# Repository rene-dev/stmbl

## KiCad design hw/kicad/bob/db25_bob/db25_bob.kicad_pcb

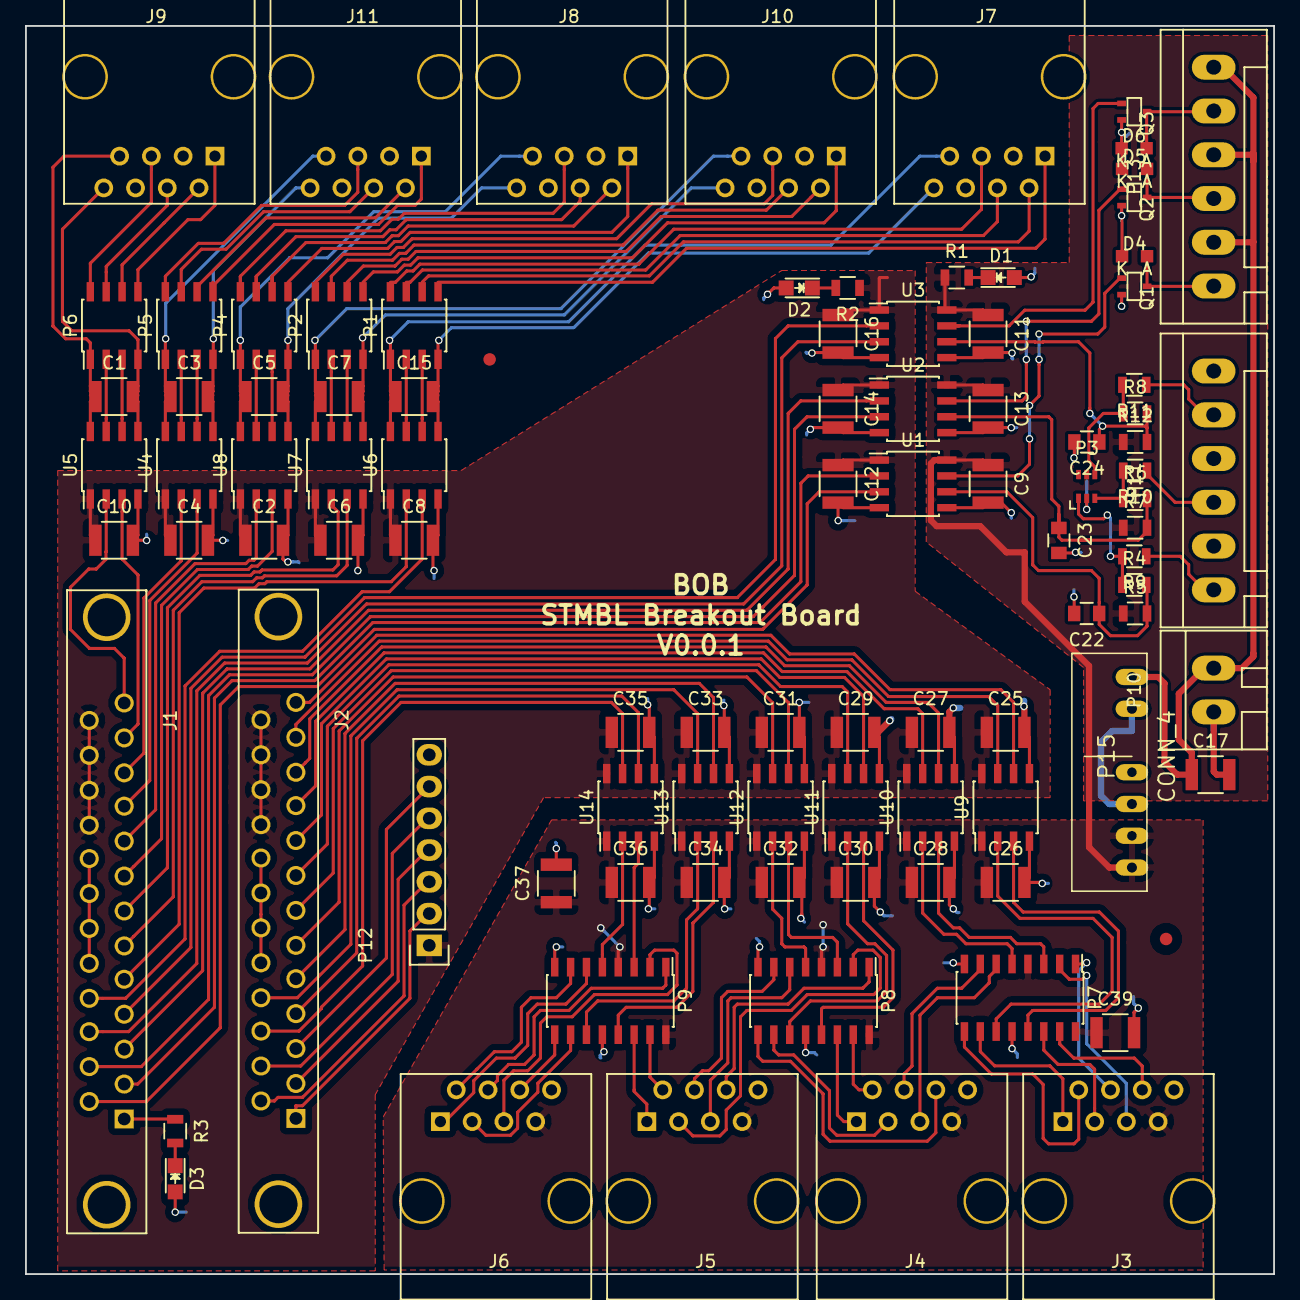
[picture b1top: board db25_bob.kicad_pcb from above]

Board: 2 copper layers, 99.8 x 99.8 mm, 94 parts (0 on the bottom side), 133 nets.

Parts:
C1, C2, C3, C4, C5, C6, C7, C8, C9, C10, C11, C12, C13, C14, C15, C16, C17, C25, C26, C27, C28, C29, C30, C31, C32, C33, C34, C35, C36, C37, C39: C; C_1210
C22, C23, C24: C; C_0805
D1, D2, D3: LED; LED-0805
D4, D5, D6: DIODE; MiniMELF_Standard
J1, J2: DB25; DB25FD
J3, J4, J5, J6, J7, J8, J9, J10, J11: RJ45; RJ45_8
P1, P2, P4, P5, P6: DIL8; SOIC-8_3.9x4.9mm_Pitch1.27mm
P3: DIL6; SC-70-6
P7, P8, P9: DIL16; SOIC-16_3.9x9.9mm_Pitch1.27mm
P10: CONN_2; WAGO_734_2pin_Straight_RuggedPads
P11, P13: CONN_6; WAGO_734_6pin_Straight_RuggedPads
P12: CONN_7; Socket_Strip_Straight_1x07
P15: CONN_4; SIP7
Q1, Q2, Q3: FET_N; sc70
R1, R2, R3, R4, R5, R6, R7, R8, R9, R10, R11, R12: R; R_0805
U1, U2, U3, U4, U5, U6, U7, U8: ADuM1201WT; SOIC-8_3.9x4.9mm_Pitch1.27mm
U9, U10, U11, U12, U13, U14: ADuM1200CR; SOIC-8_3.9x4.9mm_Pitch1.27mm

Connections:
0RX: P1.2, U6.7
0RX+: J7.5, P1.8
0RX-: J7.4, P1.7
0TX: P1.3, U6.6
0TX+: J7.1, P1.5
0TX-: J7.2, P1.6
1RX: P2.2, U7.7
1RX+: J10.5, P2.8
1RX-: J10.4, P2.7
1TX: P2.3, U7.6
1TX+: J10.1, P2.5
1TX-: J10.2, P2.6
2RX: P4.2, U8.7
2RX+: J8.5, P4.8
2RX-: J8.4, P4.7
2TX: P4.3, U8.6
2TX+: J8.1, P4.5
2TX-: J8.2, P4.6
3RX: P5.2, U4.7
3RX+: J11.5, P5.8
3RX-: J11.4, P5.7
3TX: P5.3, U4.6
3TX+: J11.1, P5.5
3TX-: J11.2, P5.6
4RX: P6.2, U5.7
4RX+: J9.5, P6.8
4RX-: J9.4, P6.7
4TX: P6.3, U5.6
4TX+: J9.1, P6.5
4TX-: J9.2, P6.6
5V0: C15.1, J7.7, P1.1, U6.8
5V1: C7.1, J10.7, P2.1, U7.8
5V2: C5.1, J8.7, P4.1, U8.8
5V3: C3.1, J11.7, P5.1, U4.8
5V4: C1.1, J9.7, P6.1, U5.8
+5V: C2.1, C4.1, C6.1, C8.1, C10.1, C12.1, C14.1, C16.1, C25.1, C27.1, C29.1, C31.1, C33.1, C35.1, J1.22, J1.23, J1.24, J1.25, J2.22, J2.23, J2.24, J2.25, P12.1, R2.1, U1.1, U2.1, U3.1, U4.1, U5.1, U6.1, U7.1, U8.1, U9.8, U10.8, U11.8, U12.8, U13.8, U14.8
+5VA: C9.1, C11.1, C13.1, C26.1, C28.1, C30.1, C32.1, C34.1, C36.1, C37.1, C39.1, J3.7, J4.7, J5.7, J6.7, P3.5, P7.4, P7.16, P8.4, P8.16, P9.4, P9.16, P15.4, R1.1, R5.1, R7.1, R12.1, U1.8, U2.8, U3.8, U9.1, U10.1, U11.1, U12.1, U13.1, U14.1
+24V: C17.1, P10.2, P13.2, P13.4, P13.6, P15.1
EN-: C9.2, C11.2, C13.2, C17.2, C22.2, C23.2, C24.2, C26.2, C28.2, C30.2, C32.2, C34.2, C36.2, C37.2, C39.2, D1.2, D4.1, D5.1, D6.1, J3.8, J4.8, J5.8, J6.8, P3.2, P7.8, P7.12, P8.8, P8.12, P9.8, P9.12, P10.1, P11.2, P11.4, P11.6, P15.2, P15.3, Q1.S, Q2.S, Q3.S, U1.5, U2.5, U3.5, U9.4, U10.4, U11.4, U12.4, U13.4, U14.4
ENC0A: P7.11, U9.2
ENC0A+: J3.1, P7.10
ENC0A-: J3.2, P7.9
ENC0AO: J2.12, U9.7
ENC0B: P7.13, U9.3
ENC0B+: J3.3, P7.14
ENC0B-: J3.6, P7.15
ENC0BO: J2.13, U9.6
ENC0Z: P7.3, U10.3
ENC0Z+: J3.5, P7.2
ENC0Z-: J3.4, P7.1
ENC0ZO: J2.11, U10.6
ENC1A: P8.13, U11.3
ENC1A+: J4.1, P8.14
ENC1A-: J4.2, P8.15
ENC1AO: J2.9, U11.6
ENC1B: P8.11, U11.2
ENC1B+: J4.3, P8.10
ENC1B-: J4.6, P8.9
ENC1BO: J2.8, U11.7
ENC1Z: P7.5, U10.2
ENC1Z+: J4.5, P7.6
ENC1Z-: J4.4, P7.7
ENC1ZO: J2.10, U10.7
ENC2A: P9.13, U13.3
ENC2A+: J5.1, P9.14
ENC2A-: J5.2, P9.15
ENC2AO: J2.5, U13.6
ENC2B: P8.3, U12.3
ENC2B+: J5.3, P8.2
ENC2B-: J5.6, P8.1
ENC2BO: J2.7, U12.6
ENC2Z: P8.5, U12.2
ENC2Z+: J5.5, P8.6
ENC2Z-: J5.4, P8.7
ENC2ZO: J2.6, U12.7
ENC3A: P9.5, U14.2
ENC3A+: J6.1, P9.6
ENC3A-: J6.2, P9.7
ENC3AO: J2.16, U14.7
ENC3B: P9.11, U13.2
ENC3B+: J6.3, P9.10
ENC3B-: J6.6, P9.9
ENC3BO: J2.17, U13.7
ENC3Z: P9.3, U14.3
ENC3Z+: J6.5, P9.2
ENC3Z-: J6.4, P9.1
ENC3ZO: J2.4, U14.6
GND: C2.2, C4.2, C6.2, C8.2, C10.2, C12.2, C14.2, C16.2, C25.2, C27.2, C29.2, C31.2, C33.2, C35.2, D2.2, D3.2, J1.18, J1.19, J1.20, J1.21, J2.18, J2.19, J2.20, J2.21, P12.7, U1.4, U2.4, U3.4, U4.4, U5.4, U6.4, U7.4, U8.4, U9.5, U10.5, U11.5, U12.5, U13.5, U14.5
GND0: C15.2, J7.8, P1.4, U6.5
GND1: C7.2, J10.8, P2.4, U7.5
GND2: C5.2, J8.8, P4.4, U8.5
GND3: C3.2, J11.8, P5.4, U4.5
GND4: C1.2, J9.8, P6.4, U5.5
IN0: P11.1, R9.1
IN0P: C22.1, R4.2, R5.2, U1.6
IN0R: P3.1, R4.1, R9.2
IN1: P11.3, R10.1
IN1P: C23.1, R6.2, R7.2, U2.6
IN1R: P3.3, R6.1, R10.2
IN2: P11.5, R11.1
IN2P: C24.1, R8.2, R12.2, U3.6
IN2R: P3.4, R8.1, R11.2
IO0: J1.17, U6.3
IO1: J1.5, U6.2
IO2: J1.6, U7.3
IO3: J1.7, U7.2
IO4: J1.8, U8.3
IO5: J1.9, U8.2
IO6: J1.10, U4.3
IO7: J1.11, U4.2
IO8: J1.12, U5.3
IO9: J1.13, U5.2
IO10: J1.14, U1.3
IO11: J1.2, U1.2
IO12: J1.15, U2.3
IO13: J1.3, U2.2
IO14: J1.16, U3.3
IO15: J1.4, U3.2
IO16: J1.1, R3.1
unnamed: D1.1, R1.2
unnamed: D2.1, R2.2
unnamed: D3.1, R3.2
unnamed: J2.1, P12.2
unnamed: J2.2, P12.4
unnamed: J2.3, P12.6
unnamed: J2.14, P12.3
unnamed: J2.15, P12.5
OUT0: Q1.G, U1.7
OUT0FET: D4.2, P13.1, Q1.D
OUT1: Q2.G, U2.7
OUT1FET: D5.2, P13.3, Q2.D
OUT2: Q3.G, U3.7
OUT2FET: D6.2, P13.5, Q3.D

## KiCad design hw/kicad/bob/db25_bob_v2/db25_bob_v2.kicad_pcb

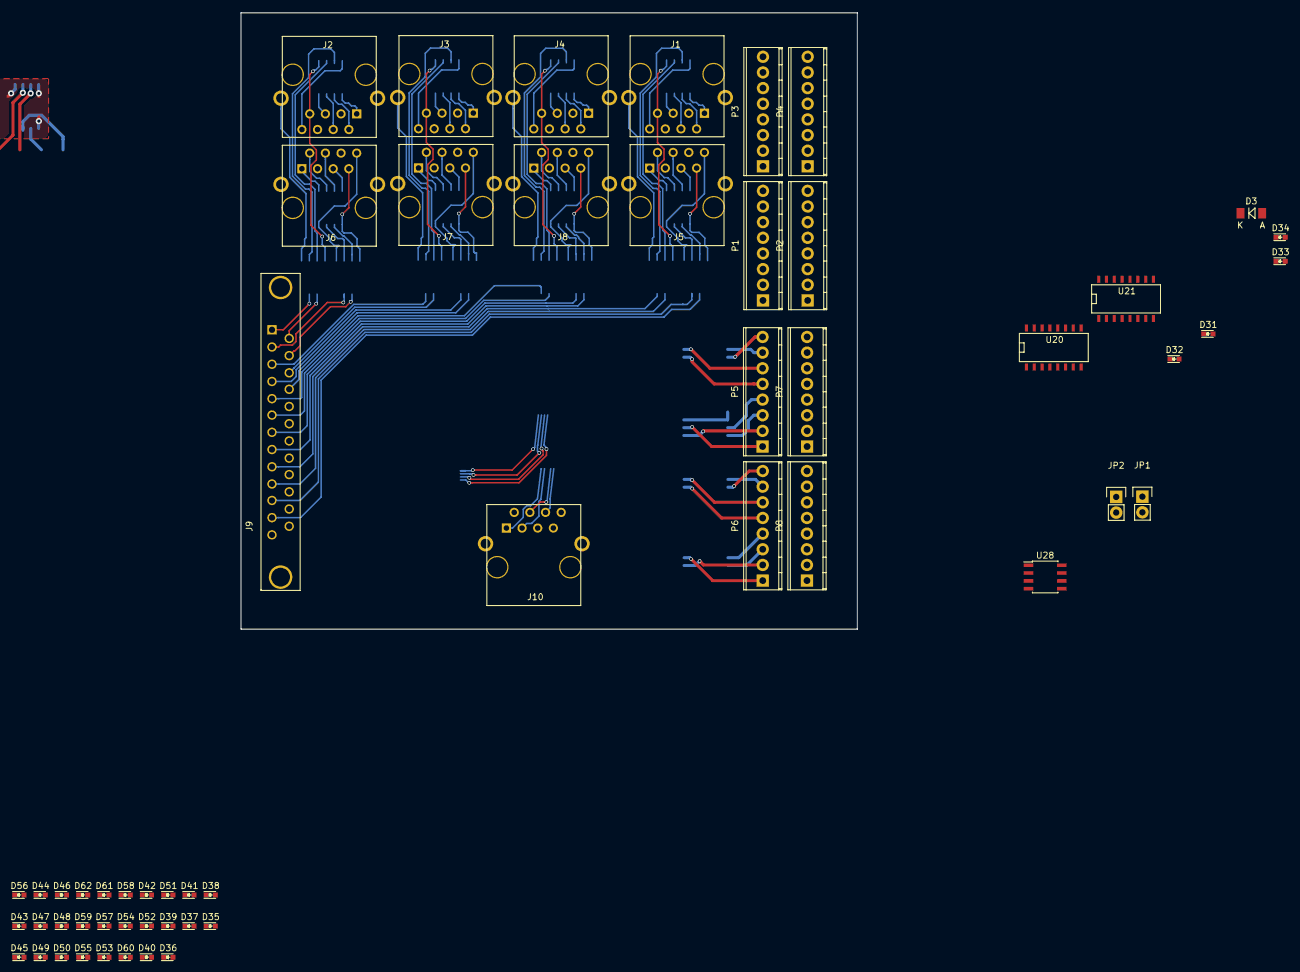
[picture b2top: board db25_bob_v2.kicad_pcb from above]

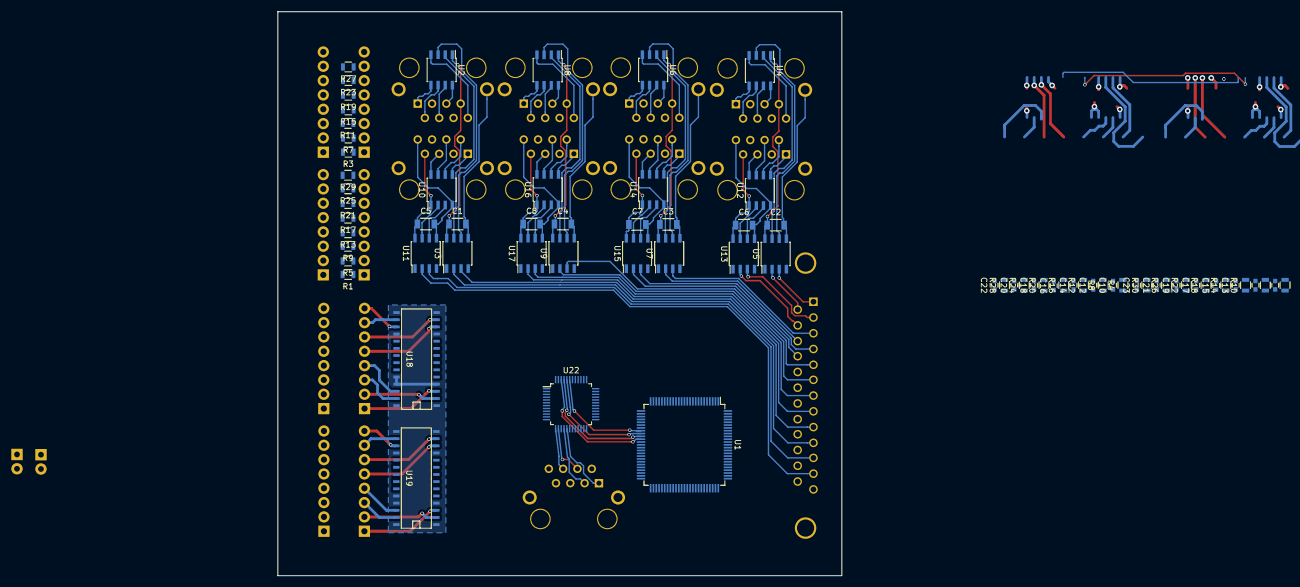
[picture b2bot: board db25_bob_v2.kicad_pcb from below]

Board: 2 copper layers, 100.0 x 100.0 mm, 129 parts (73 on the bottom side), 157 nets.

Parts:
C1, C2, C3, C4, C5, C6, C7, C8: C; C_1206
C9, C10, C11, C12, C13, C14, C15, C16, C17, C18, C19, C20, C21, C22, C23: C; C_0603
D3: D; MiniMELF_Standard
D31, D32, D33, D34, D35, D36, D37, D38, D39, D40, D41, D42, D43, D44, D45, D46, D47, D48, D49, D50, D51, D52, D53, D54, D55, D56, D57, D58, D59, D60, D61, D62: LED; LED_0603
J1, J2, J3, J4, J5, J6, J7, J8: RJ45; MHRJJ88NFVS
J9: DB25; DB25FD
J10: RJ45-TRANSFO; MHRJJ88NFVS
JP1, JP2: JUMPER; Pin_Header_Straight_1x02
P1, P2, P3, P4, P5, P6, P7, P8: CONN_01X08; TerminalBlock_Pheonix_MPT-2.54mm_8pol
R1, R2, R3, R4, R5, R6, R7, R8, R9, R10, R11, R12, R13, R14, R15, R16, R17, R18, R19, R20, R21, R22, R23, R24, R25, R26, R27, R28, R29, R30: R; R_0805
U1: STM32F407VG; TQFP-100_14x14mm_Pitch0.5mm
U2, U4, U6, U8, U10, U12, U14, U16: ADM4857; SOIC-8_3.9x4.9mm_Pitch1.27mm
U3, U5, U7, U9, U11, U13, U15, U17, U28: ADuM1201WT; SOIC-8_3.9x4.9mm_Pitch1.27mm
U18, U19: NCV7608; SOIC-28
U20, U21: 74HC595; SO-16-N
U22: DP83848C; LQFP-48_7x7mm_Pitch0.5mm

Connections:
5V1: C2.1, J2.7, U4.1, U5.8
5V2: C6.1, J6.7, U12.1, U13.8
5V3: C3.1, J3.7, U6.1, U7.8
5V4: C7.1, J7.7, U14.1, U15.8
5V5: C4.1, J4.7, U8.1, U9.8
5V6: C8.1, J8.7, U16.1, U17.8
5V7: C1.1, J1.7, U2.1, U3.8
5V8: C5.1, J5.7, U10.1, U11.8
+3V3: D3.1, U18.8, U19.8
+5VD: J9.22, J9.23, J9.24, J9.25, U3.1, U5.1, U7.1, U9.1, U11.1, U13.1, U15.1, U17.1, U28.1
+24V: U18.1, U18.4, U18.11, U18.14, U18.15, U18.18, U18.24, U18.25, U18.28, U19.1, U19.4, U19.11, U19.14, U19.15, U19.18, U19.24, U19.25, U19.28
AIN1: P1.1, R1.2
AIN2: P1.2, R5.2
AIN3: P1.3, R9.2
AIN4: P1.4, R13.2
AIN5: P1.5, R17.2
AIN6: P1.6, R21.2
AIN7: P1.7, R25.2
AIN8: P1.8, R29.2
AIN9: P3.1, R3.2
AIN10: P3.2, R7.2
AIN11: P3.3, R11.2
AIN12: P3.4, R15.2
AIN13: P3.5, R19.2
AIN14: P3.6, R23.2
AIN15: P3.7, R27.2
CSB: U18.5, U19.5
EN: U18.19, U19.19
GND: C9.2, C10.2, C11.2, C12.2, C13.2, C14.2, C15.2, C16.2, C17.2, C18.2, C19.2, C20.2, C21.2, C22.2, C23.2, P2.1, P2.2, P2.3, P2.4, P2.5, P2.6, P2.7, P2.8, P4.1, P4.2, P4.3, P4.4, P4.5, P4.6, P4.7, P4.8, P7.1, P7.2, P7.3, P7.4, P7.5, P7.6, P7.7, P7.8, P8.1, P8.2, P8.3, P8.4, P8.5, P8.6, P8.7, P8.8, R2.2, R4.2, R6.2, R8.2, R10.2, R12.2, R14.2, R16.2, R18.2, R20.2, R22.2, R24.2, R26.2, R28.2, R30.2, U18.10, U19.10, U20.8, U21.8
GND1: C2.2, J2.8, U4.4, U5.5
GND2: C6.2, J6.8, U12.4, U13.5
GND3: C3.2, J3.8, U6.4, U7.5
GND4: C7.2, J7.8, U14.4, U15.5
GND5: C4.2, J4.8, U8.4, U9.5
GND6: C8.2, J8.8, U16.4, U17.5
GND7: C1.2, J1.8, U2.4, U3.5
GND8: C5.2, J5.8, U10.4, U11.5
GNDD: J9.18, J9.19, J9.20, J9.21, U3.4, U5.4, U7.4, U9.4, U11.4, U13.4, U15.4, U17.4, U28.4
IN0: J9.1, U5.3
IN1: J9.2, U13.3
IN1_ADC: C9.1, R1.1, R2.1
IN2: J9.3, U7.3
IN2_ADC: C11.1, R5.1, R6.1
IN3: J9.4, U15.3
IN3_ADC: C13.1, R9.1, R10.1
IN4: J9.5, U9.3
IN4_ADC: C15.1, R13.1, R14.1
IN5: J9.7, U17.3
IN5_ADC: C17.1, R17.1, R18.1
IN6: J9.9, U3.3
IN6_ADC: C19.1, R21.1, R22.1
IN7: J9.11, JP1.1, U11.3
IN7_ADC: C21.1, R25.1, R26.1
IN9_ADC: C10.1, D3.2, R3.1, R4.1
IN10_ADC: C12.1, R7.1, R8.1
IN11_ADC: C14.1, R11.1, R12.1
IN12_ADC: C16.1, R15.1, R16.1
IN13_ADC: C18.1, R19.1, R20.1
IN14_ADC: C20.1, R23.1, R24.1
IN15_ADC: C22.1, R27.1, R28.1
IN18ADC: C23.1, R29.1, R30.1
unnamed: J1.1, U2.5
unnamed: J1.2, U2.6
unnamed: J1.4, U2.7
unnamed: J1.5, U2.8
unnamed: J2.1, U4.5
unnamed: J2.2, U4.6
unnamed: J2.4, U4.7
unnamed: J2.5, U4.8
unnamed: J3.1, U6.5
unnamed: J3.2, U6.6
unnamed: J3.4, U6.7
unnamed: J3.5, U6.8
unnamed: J4.1, U8.5
unnamed: J4.2, U8.6
unnamed: J4.4, U8.7
unnamed: J4.5, U8.8
unnamed: J5.1, U10.5
unnamed: J5.2, U10.6
unnamed: J5.4, U10.7
unnamed: J5.5, U10.8
unnamed: J6.1, U12.5
unnamed: J6.2, U12.6
unnamed: J6.4, U12.7
unnamed: J6.5, U12.8
unnamed: J7.1, U14.5
unnamed: J7.2, U14.6
unnamed: J7.4, U14.7
unnamed: J7.5, U14.8
unnamed: J8.1, U16.5
unnamed: J8.2, U16.6
unnamed: J8.4, U16.7
unnamed: J8.5, U16.8
unnamed: JP1.2, U28.3
unnamed: JP2.2, U28.2
unnamed: U2.2, U3.7
unnamed: U2.3, U3.6
unnamed: U4.2, U5.7
unnamed: U4.3, U5.6
unnamed: U6.2, U7.7
unnamed: U6.3, U7.6
unnamed: U8.2, U9.7
unnamed: U8.3, U9.6
unnamed: U10.2, U11.7
unnamed: U10.3, U11.6
unnamed: U12.2, U13.7
unnamed: U12.3, U13.6
unnamed: U14.2, U15.7
unnamed: U14.3, U15.6
unnamed: U16.2, U17.7
unnamed: U16.3, U17.6
OUT0: J9.14, U5.2
OUT1: J9.15, U13.2
OUT2: J9.16, U7.2
OUT3: J9.17, U15.2
OUT4: J9.6, U9.2
OUT5: J9.8, U17.2
OUT6: J9.10, U3.2
OUT7: J9.12, JP2.1, U11.2
R+: J10.4, U22.14
R-: J10.6, U22.13
SCK: U18.6, U19.6
SO1: U18.9, U19.7
SSOUT1: P5.1, U18.3
SSOUT2: P5.2, U18.2
SSOUT3: P5.3, U18.27
SSOUT4: P5.4, U18.26
SSOUT5: P5.5, U18.12
SSOUT6: P5.6, U18.13
SSOUT7: P5.7, U18.16
SSOUT8: P5.8, U18.17
SSOUT9: P6.1, U19.3
SSOUT10: P6.2, U19.2
SSOUT11: P6.3, U19.27
SSOUT12: P6.4, U19.26
SSOUT13: P6.5, U19.12
SSOUT14: P6.6, U19.13
SSOUT15: P6.7, U19.16
SSOUT16: P6.8, U19.17
T+: J10.1, U22.17
T-: J10.3, U22.16
VCC: U20.16, U21.16
col: U1.26, U22.42
mdc: U1.16, U22.31
mdio: U1.25, U22.30
rx_clk: U1.24, U22.38
rx_d0: U1.33, U22.43
rx_d1: U1.34, U22.44
rx_d2: U1.35, U22.45
rx_d3: U1.36, U22.46
rx_dv: U1.32, U22.39
tx_clk: U1.18, U22.1
tx_d0: U1.51, U22.3
tx_d1: U1.52, U22.4
tx_d2: U1.17, U22.5
tx_d3: U1.95, U22.6
tx_en: U1.48, U22.2

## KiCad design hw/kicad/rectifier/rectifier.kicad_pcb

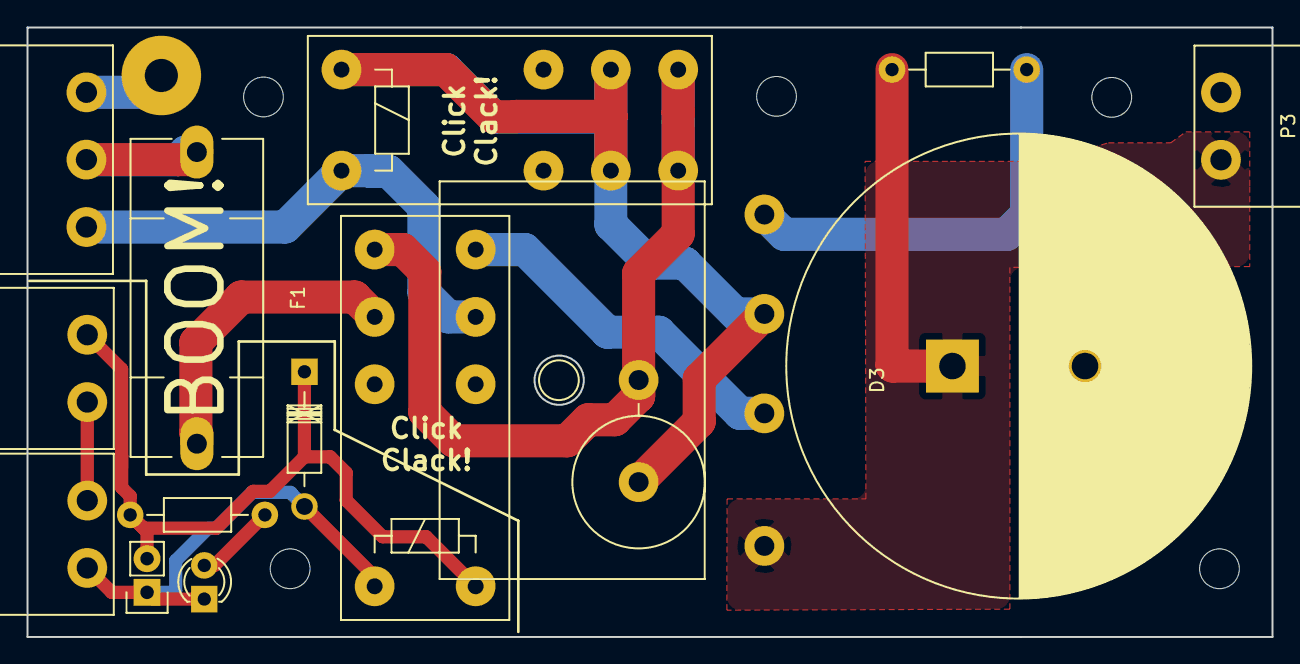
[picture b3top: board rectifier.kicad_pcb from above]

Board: 2 copper layers, 93.9 x 46.0 mm, 16 parts (0 on the bottom side), 13 nets.

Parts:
C1: CP1; C_Radial_D35_L51_P10
D1: LED; LED-3MM
D2: DIODE; Diode_DO-41_SOD81_Horizontal_RM10
D3: BRIDGE; dfb_bridge
F1: FUSE; Fuseholder5x20_horiz_SemiClosed_Casing10x25mm
K1: CONN_3; WE313-3
P1, P2, P3: CONN_2; WE313-2
P4: CONN_2; Socket_Strip_Straight_1x02
P5: CONN_1; SolderWirePad_single_2-5mmDrill
R1, R3: R; Resistor_Horizontal_RM10mm
R2: R; Resistor_Vertical_RM7.5mm
RL1, RL2: FINDER-40.52; Relay_DPDT_Schrack-RT2_RM5mm

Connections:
AC_fused: F1.2, RL2.11
AC_ntc: D3.4, R2.1, RL1.11, RL1.21, RL1.A1
AC_switched: R2.2, RL1.14, RL1.24, RL2.14
DC+: C1.1, D3.3, P3.1, R3.1
DC-: C1.2, D3.1, P3.2, R3.2
unnamed: D1.1, D2.2, P1.2, P4.1, RL2.A1
unnamed: D1.2, R1.1
unnamed: D2.1, P2.1, P4.2, R1.2, RL2.A2
unnamed: F1.1, K1.2
unnamed: P1.1, P2.2
Neutral: K1.3, RL1.A2, RL2.21
Neutral_Switched: D3.2, RL2.24
PE: K1.1, P5.1

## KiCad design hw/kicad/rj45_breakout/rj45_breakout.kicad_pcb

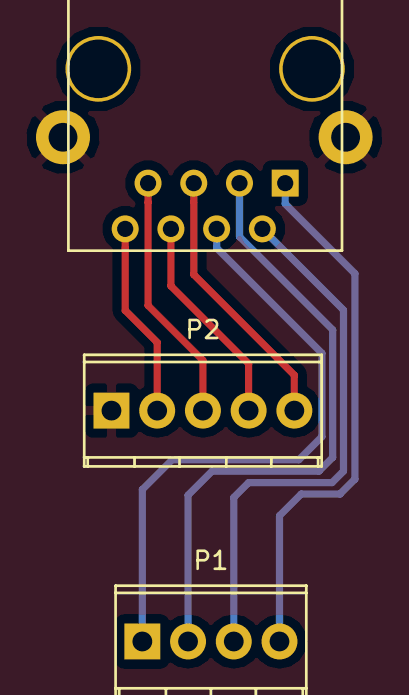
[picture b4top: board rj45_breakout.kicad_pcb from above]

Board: 2 copper layers, 3 parts (0 on the bottom side), 9 nets.

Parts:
J1: RJ45; RJ45_8
P1: CONN_4; TerminalBlock_Pheonix_MPT-2.54mm_4pol
P2: CONN_5; TerminalBlock_Pheonix_MPT-2.54mm_5pol

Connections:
unnamed: J1.1, P1.4
unnamed: J1.2, P1.3
unnamed: J1.3, P1.2
unnamed: J1.4, P1.1
unnamed: J1.5, P2.5
unnamed: J1.6, P2.4
unnamed: J1.7, P2.3
unnamed: J1.8, P2.2
unnamed: J1.9, P2.1

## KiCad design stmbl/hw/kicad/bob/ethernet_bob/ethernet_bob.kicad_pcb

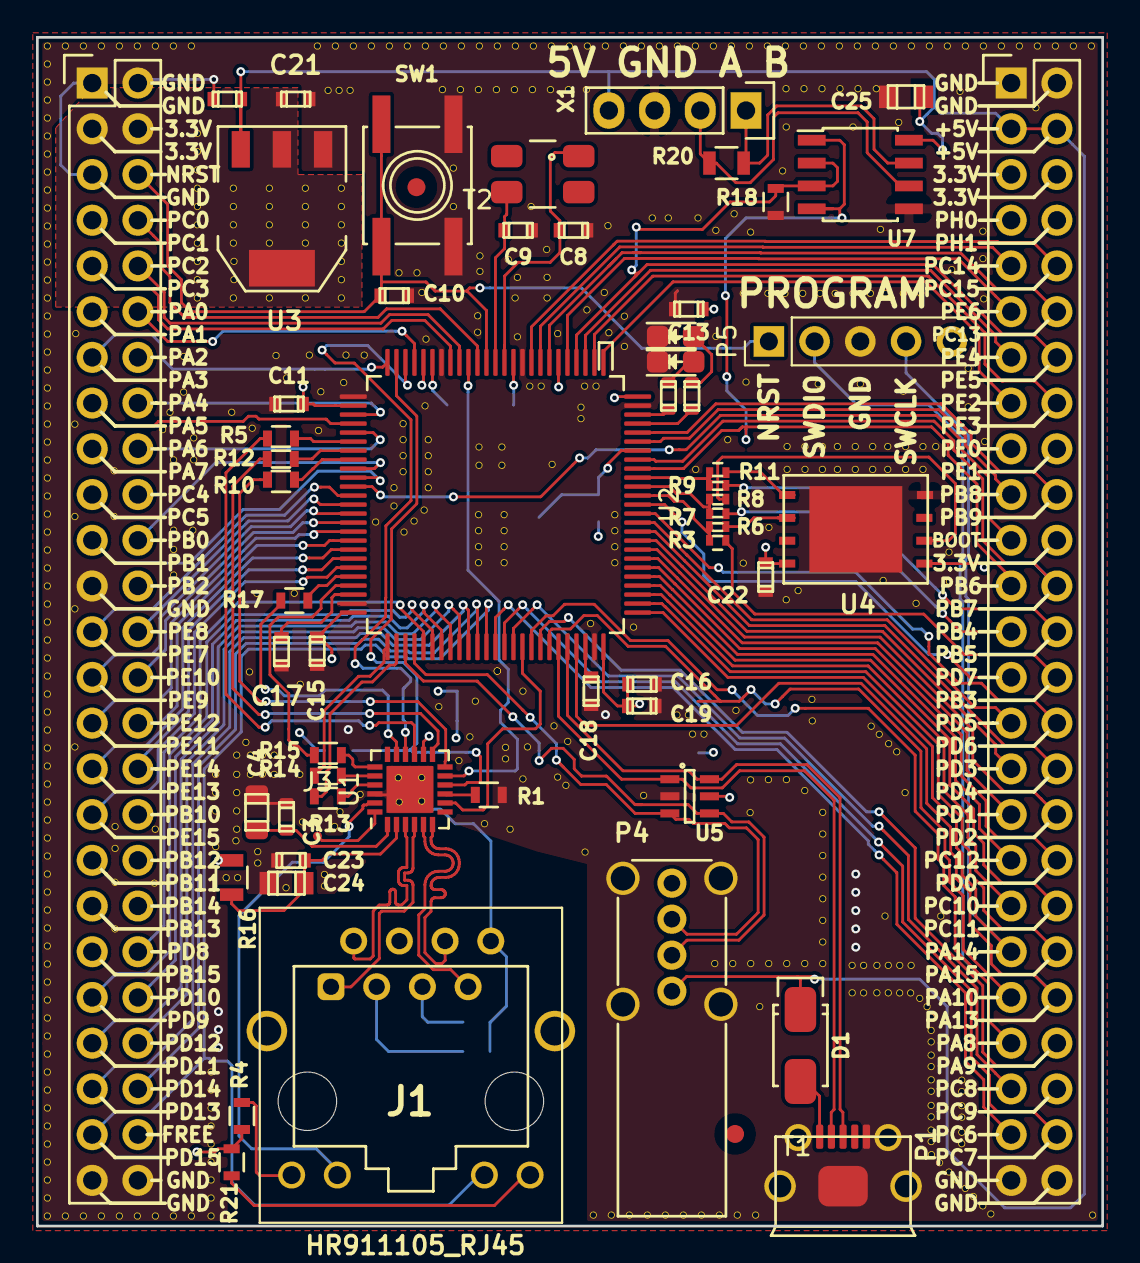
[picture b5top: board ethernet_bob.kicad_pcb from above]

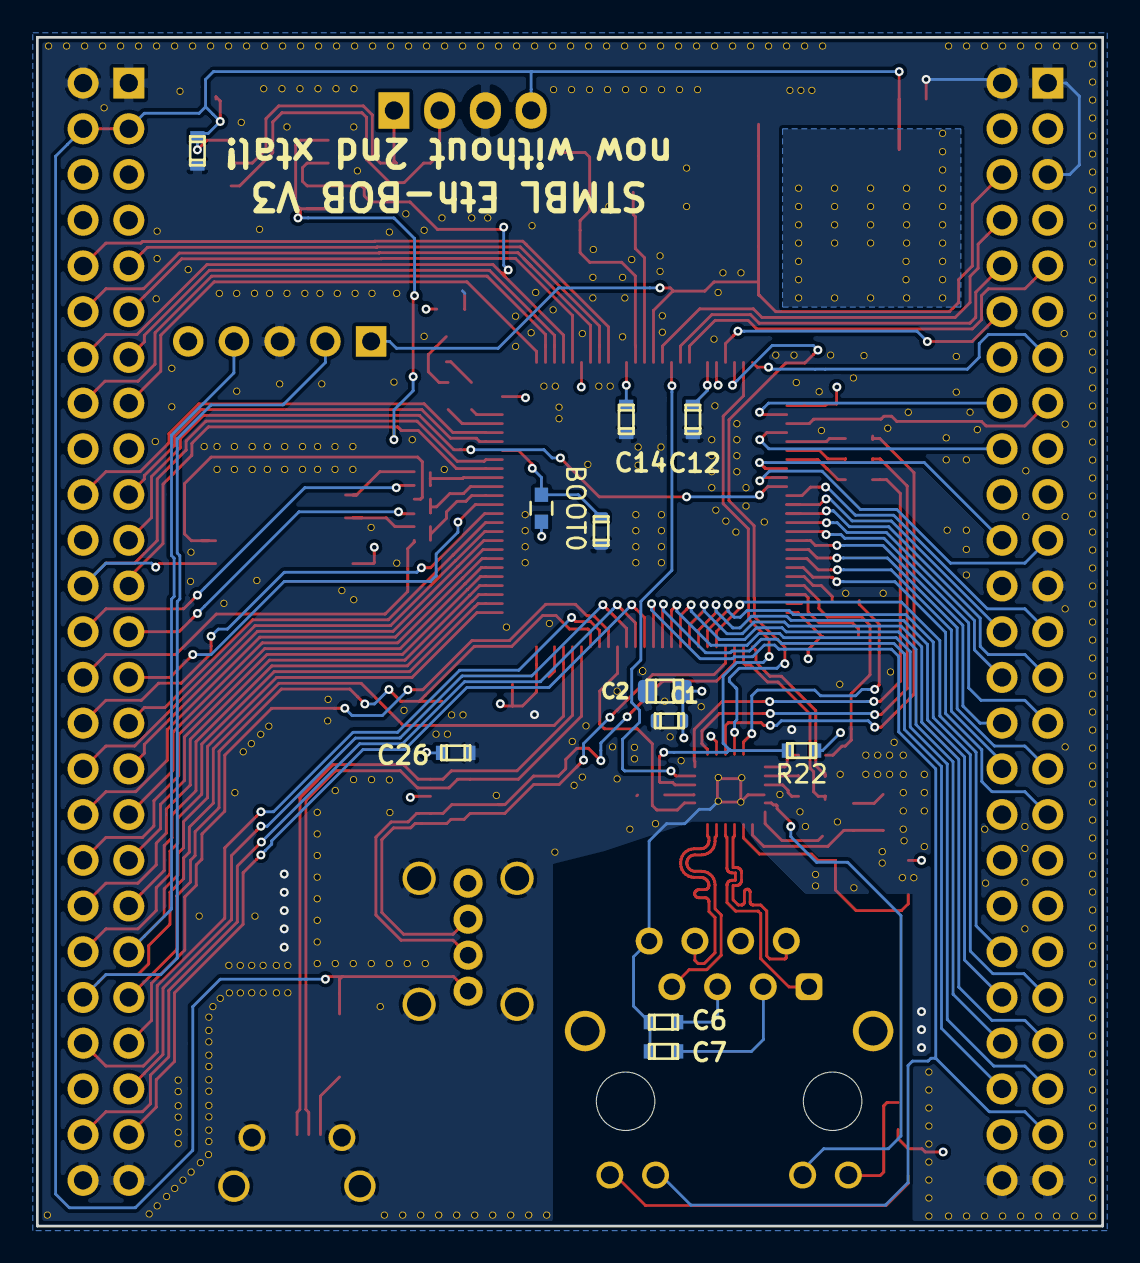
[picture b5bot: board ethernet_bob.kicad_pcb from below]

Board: 4 copper layers, 59.2 x 66.0 mm, 71 parts (11 on the bottom side), 120 nets.

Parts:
C1, C3, C6, C7, C11, C12, C13, C14, C15, C16, C17, C18, C19, C23, C26: 100n; C_0603
C2, C4, C24: 22µ; C_0805
C5, C10, C20, C21, C22: C; C_0603
C8, C9: 18pF; C_0603
C25: C; C_0805
D1: D_Schottky; SMA_Standard
D2, D3: LED; LED-0805
J1: HR911105_RJ45; HY951180A_RJ45
J3: CONN_01X01; Measurement_Point_Round-SMD-Pad_Big
JP1: BOOT0; C_0603
P1: USB_OTG; USB_Micro-B
P2, P3: CONN_02X25; Pin_Header_Straight_2x25
P4: USB_A; USB_A_Vertical
P5: CONN_01X04; PinHeader_1x05_P2.54mm_Vertical
P6: CONN_01X04; Pin_Header_Straight_1x04
R1: 6k49; R_0603
R3, R6, R7, R8, R9, R11: R; R_0402
R4, R21: 220; R_0603
R5, R10, R12, R13, R14, R15, R17: 1k; R_0603
R16, R20: R; R_0805
R18, R19, R22, R23, R24: R; R_0603
SW1: SW_PUSH; SW_SPST_EVQQ2
T1, T2: testpoint; Fiducial_1mm_Outer_CopperTop
U1: KSZ8081; QFN-24-1EP_4x4mm_Pitch0.5mm
U2: STM32F407VETx; LQFP-100_14x14mm_Pitch0.5mm
U3: NCP1117ST33T3G; SOT-223
U4: CAT250_EEPROM; MLP8_8x6
U5: USBLC6-4SC6; SOT-23-6
U7: SP3485EN; SOIC-8_3.9x4.9mm_Pitch1.27mm
X1: CRYSTAL_SMD_4pin; Crystal_SMD_0603_4Pads

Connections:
+1V2: C3.1, C4.1, U1.1
+3V3: C1.1, C2.1, C11.2, C12.2, C13.2, C14.2, C15.2, C16.2, C19.2, C21.1, C22.1, C26.2, JP1.1, P2.3, P2.4, P3.5, P3.6, P3.22, P5.5, R4.1, R16.2, R21.1, R22.1, U1.14, U2.6, U2.11, U2.20, U2.21, U2.27, U2.50, U2.75, U2.100, U3.2, U4.8, U5.5
+5VP: C5.1, C20.1, C25.1, D1.1, P3.3, P3.4, P4.1, P6.4, U3.3, U7.8
/Phy and RJ45/LED1A: J1.9, R4.2
/Phy and RJ45/LED1K: J1.10, U1.23
/Phy and RJ45/LED2A: J1.12, R21.2
/Phy and RJ45/PHY_CRS: R5.2, U2.31
/Phy and RJ45/PHY_MDC: U1.11, U2.16
/Phy and RJ45/PHY_MDIO: R22.2, U1.10, U2.24
/Phy and RJ45/PHY_REFCLK: U1.16, U2.23
/Phy and RJ45/PHY_RST: J3.1, U1.24
/Phy and RJ45/PHY_RXD0: R12.2, U2.32
/Phy and RJ45/PHY_RXD1: R10.2, U2.33
/Phy and RJ45/PHY_RXER: R17.1, U2.46
/Phy and RJ45/PHY_TXD0: R14.1, U2.51
/Phy and RJ45/PHY_TXD1: R13.1, U2.52
/Phy and RJ45/PHY_TXEN: R15.1, U2.47
/Phy and RJ45/PHY_XI: U1.8, U2.66
/flash/FLASH_MISO: R8.1, U4.2
/flash/FLASH_MOSI: R11.1, U4.5
/flash/FLASH_SCK: R6.1, U4.6
BOOT1: P3.21, U2.36
GND: C1.2, C2.2, C3.2, C4.2, C5.2, C6.2, C7.2, C8.2, C9.2, C10.2, C11.1, C12.1, C13.1, C14.1, C15.1, C16.1, C17.1, C18.1, C19.1, C20.2, C21.2, C22.2, C23.2, C24.2, C25.2, C26.1, D2.1, D3.1, J1.8, P1.5, P1.6, P2.1, P2.2, P2.5, P2.23, P2.49, P2.50, P3.1, P3.2, P3.49, P3.50, P4.5, P5.3, P6.3, R1.2, R18.2, R19.2, SW1.1, U1.22, U1.25, U2.10, U2.19, U2.26, U2.49, U2.74, U2.99, U3.1, U4.4, U5.2, U7.5
LED2: J1.11, P2.47, U2.62
NRST: C10.1, P2.6, P5.1, SW1.2, U2.14
unnamed: C6.1, J1.5
unnamed: C7.1, J1.3
unnamed: C8.1, U2.12, X1.1
unnamed: C9.1, U2.13, X1.2
unnamed: C17.2, U2.48
unnamed: C18.2, U2.73
unnamed: D1.2, P1.1
unnamed: D2.2, R23.2
unnamed: D3.2, R24.2
unnamed: JP1.2, R19.1, U2.94
unnamed: P6.1, R20.2, U7.7
unnamed: P6.2, R20.1, U7.6
unnamed: R1.1, U1.9
unnamed: R3.2, R6.2, U2.89
unnamed: R5.1, U1.15
unnamed: R7.2, R8.2, U2.90
unnamed: R10.1, U1.12
unnamed: R9.2, R11.2, U2.91
unnamed: R12.1, U1.13
unnamed: R13.2, U1.21
unnamed: R14.2, U1.20
unnamed: R15.2, U1.19
unnamed: R17.2, U1.17
unnamed: R23.1, U2.97
unnamed: R24.1, U2.98
PA0: P2.12, U2.22
PA3: P2.13, U2.25
PA4: P2.16, U2.28
PA5: P2.15, U2.29
PA6: P2.18, U2.30
PA8: P3.43, U2.67
PA9: P3.44, U2.68
PA10: P3.41, U2.69
PA13: P3.42, P5.2, U2.72
PA14: P3.39, P5.4, U2.76
PA15: P3.40, U2.77
PB0: P2.22, U2.34
PB1: P2.21, U2.35
PB3: P3.28, R3.1
PB4: P3.25, R7.1
PB5: P3.26, R9.1
PB6: P3.23, U2.92, U7.1, U7.4
PB7: P3.24, U2.93, U4.1
PB8: P3.19, U2.95
PB9: P3.20, U2.96
PC0: P2.8, U2.15
PC2: P2.10, U2.17
PC3: P2.9, U2.18
PC6: P3.47, U2.63
PC7: P3.48, U2.64
PC8: P3.45, U2.65
PC10: P3.37, U2.78
PC11: P3.38, U2.79
PC12: P3.35, U2.80
PC13: P3.12, U2.7
PC14: P3.9, U2.8
PC15: P3.10, U2.9
PD0: P3.36, U2.81
PD1: P3.33, U2.82
PD2: P3.34, U2.83
PD3: P3.31, U2.84
PD4: P3.32, U2.85
PD5: P3.29, U2.86
PD6: P3.30, U2.87
PD7: P3.27, U2.88
PD8: P2.40, U2.55
PD9: P2.41, U2.56
PD10: P2.42, U2.57
PD11: P2.43, U2.58
PD12: P2.44, U2.59
PD13: P2.45, U2.60
PD14: P2.46, U2.61
PE2: P3.15, U2.1
PE3: P3.16, U2.2
PE4: P3.13, U2.3
PE5: P3.14, R18.1, U2.4, U7.2, U7.3
PE6: P3.11, U2.5
PE7: P2.25, U2.37
PE8: P2.26, U2.38
PE9: P2.27, U2.39
PE10: P2.28, U2.40
PE11: P2.29, U2.41
PE12: P2.30, U2.42
PE13: P2.31, U2.43
PE14: P2.32, U2.44
PE15: P2.33, U2.45
RX_N: J1.2, U1.3
RX_P: J1.1, U1.4
TX_N: J1.7, U1.5
TX_P: J1.6, U1.6
USB+: P1.3, U2.71, U5.6
USB-: P1.2, U2.70, U5.1
USB_OTG+: P4.3, U2.54, U5.3
USB_OTG-: P4.2, U2.53, U5.4
VDDA: C23.1, C24.1, R16.1, U1.2
